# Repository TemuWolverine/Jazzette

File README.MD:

# Jazzette Player
> [!WARNING]  
> **This is work in progress**.  
> I am using this readme as a bit of a scratchpad of parts. Don't assume they're the final parts until this announcement is removed.  
> **This is work in progress**.

I got nerd sniped over on [reddit](https://www.reddit.com/r/homeassistant/comments/1vtjl21/comment/p4xepdl/).  

## PCB
PCB prototype has now been sent off for manufacture.  

## Shell
The shell is still in active development, but here is a render of the vague idea, mimicking the old cassettecorders. 

## BOM

| Part | Quantity     | Note |
|------|-------------|----- |
| [ESP32 S3 Nano](https://s.click.aliexpress.com/e/_c4tw9Hh5) | 1 ||
| [DRV8833](https://www.amazon.com.au/Xlihdzum-DRV8833-H-Bridge-Driver-Module/dp/B0GHQ6YCLV) | 1 |  |
| [N20 DC motor](https://www.aliexpress.com/item/32385310725.html) | 1 |  3v |
| [PCM5100A breakout](https://www.aliexpress.com/item/1005008889469187.html) | 1 | Headphone amp |
| [NFC breakout](https://s.click.aliexpress.com/e/_c3WaMQwL)  | 1 |  |
| [3.12" OLED (256x54) SPI](https://s.click.aliexpress.com/e/_c2IVFyqT) | 1 | White looks best IMO |
| [TOSLINK transmitter](https://s.click.aliexpress.com/e/_c3J5kkCf) | 1 |  |
| [RCA plug](https://s.click.aliexpress.com/e/_c3TPM0xV)     | 1 |       |
| 480ohm resistor    | 1 | 0803 SMD package, used for coax |
| 0.1uF capacitor    | 3 | 0803 SMD package, used for decoupling |
| 6x6 tactile switch    | 4  | SMD|
| 2 pin JST XH right angle | 2 | S2B-XH-A(LF)(SN) |
| 3 pin JST XH right angle | 1 | S3B-XH-A(LF)(SN) |
| 4 pin JST XH right angle | 1 | S4B-XH-A(LF)(SN) |
| 5 pin JST XH right angle | 1 | S5B-XH-A(LF)(SN) |
| [3-way switch](https://www.aliexpress.com/item/1005006780672833.html) | 1 |  |
| 3mm Translucent Black Acrylic | 1 | overlaid over screen |
| 3mm clear acrylic | 1 | Tape door |
| 3d printing filament | | |

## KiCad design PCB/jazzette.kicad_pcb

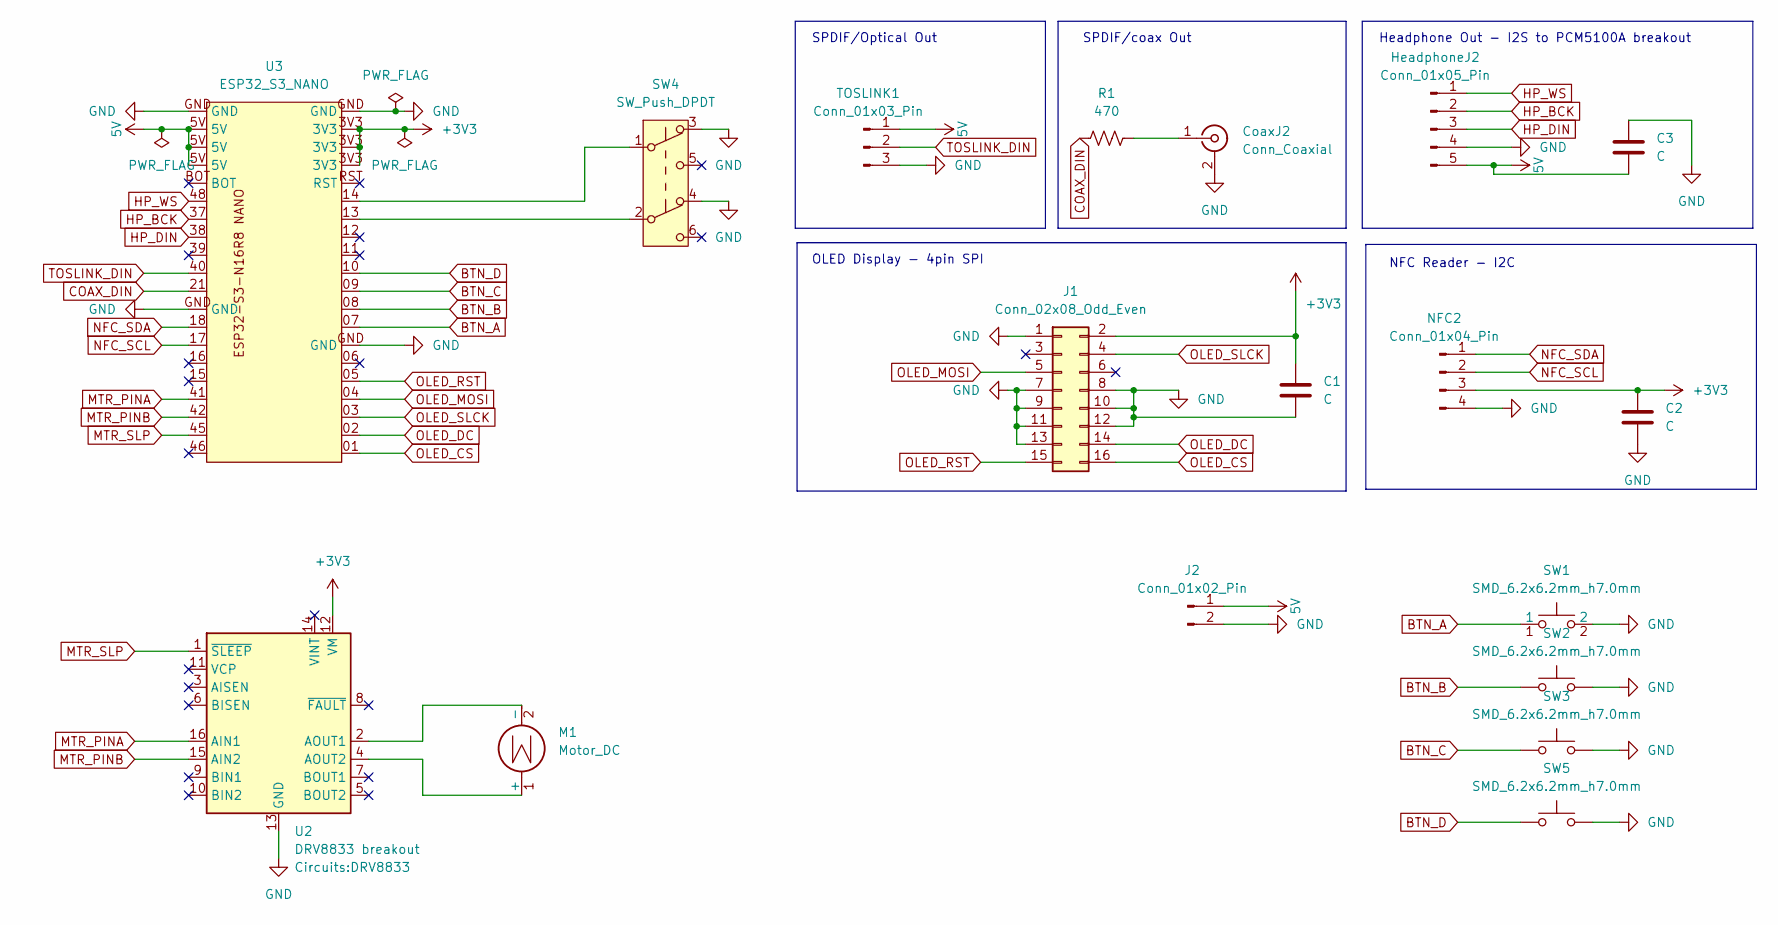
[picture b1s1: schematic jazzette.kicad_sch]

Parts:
C1, C2, C3: C; C_0805_2012Metric
CoaxJ2: Conn_Coaxial; CONN-TH_S2B-XH-A-LF-SN
HeadphoneJ2: Conn_01x05_Pin; CONN-TH_S5B-XH-A-LF-SN
J1: Conn_02x08_Odd_Even; PinSocket_2x08_P2.54mm_Vertical
J2: Conn_01x02_Pin; CONN-TH_DB125-2.54-2P-GN
M1: Motor_DC; CONN-TH_S2B-XH-A-LF-SN
NFC2: Conn_01x04_Pin; CONN-TH_S4B-XH-A-LF-SN
R1: 470; R_0603_1608Metric
SW1, SW2, SW3, SW5: SMD_6.2x6.2mm_h7.0mm; SW-SMD_SH-6X6X4.5H-TP; Mfg Part# 679-2384-2-ND
SW4: SW_Push_DPDT; PinHeader_1x04_P2.54mm_Vertical
TOSLINK1: Conn_01x03_Pin; CONN-TH_S3B-XH-A-LF-SN
U2: DRV8833 breakout; DRV8833
U3: ESP32_S3_NANO

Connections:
5V: C3.1, HeadphoneJ2.5, J2.1, TOSLINK1.1, U3.5V
+3V3: C1.1, C2.1, J1.2, NFC2.3, U2.12 (VM), U3.3V3
BTN_A: SW1.1, U3.07
BTN_B: SW2.1, U3.08
BTN_C: SW3.1, U3.09
BTN_D: SW5.1, U3.10
COAX_DIN: R1.2, U3.21
GND: C1.2, C2.2, C3.2, CoaxJ2.2 (Ext), HeadphoneJ2.4, J1.1, J1.7, J1.8, J1.9, J1.10, J1.11, J1.12, J1.13, J2.2, NFC2.4, SW1.2, SW2.2, SW3.2, SW4.3 (A), SW4.4 (A), SW5.2, TOSLINK1.3, U2.13 (GND), U3.GND
HP_BCK: HeadphoneJ2.2, U3.37
HP_DIN: HeadphoneJ2.3, U3.38
HP_WS: HeadphoneJ2.1, U3.48
MTR_PINA: U2.16 (AIN1), U3.41
MTR_PINB: U2.15 (AIN2), U3.42
MTR_SLP: U2.1 (~SLEEP), U3.45
NFC_SCL: NFC2.2, U3.17
NFC_SDA: NFC2.1, U3.18
unnamed: CoaxJ2.1 (In), R1.1
unnamed: M1.1 (+), U2.4 (AOUT2)
unnamed: M1.2 (-), U2.2 (AOUT1)
unnamed: SW4.1 (B), U3.14
unnamed: SW4.2 (B), U3.13
OLED_CS: J1.16, U3.01
OLED_DC: J1.14, U3.02
OLED_MOSI: J1.5, U3.04
OLED_RST: J1.15, U3.05
OLED_SLCK: J1.4, U3.03
TOSLINK_DIN: TOSLINK1.2, U3.40

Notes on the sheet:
SPDIF/coax Out
SPDIF/Optical Out
Headphone Out - I2S to PCM5100A breakout
NFC Reader - I2C
OLED Display - 4pin SPI

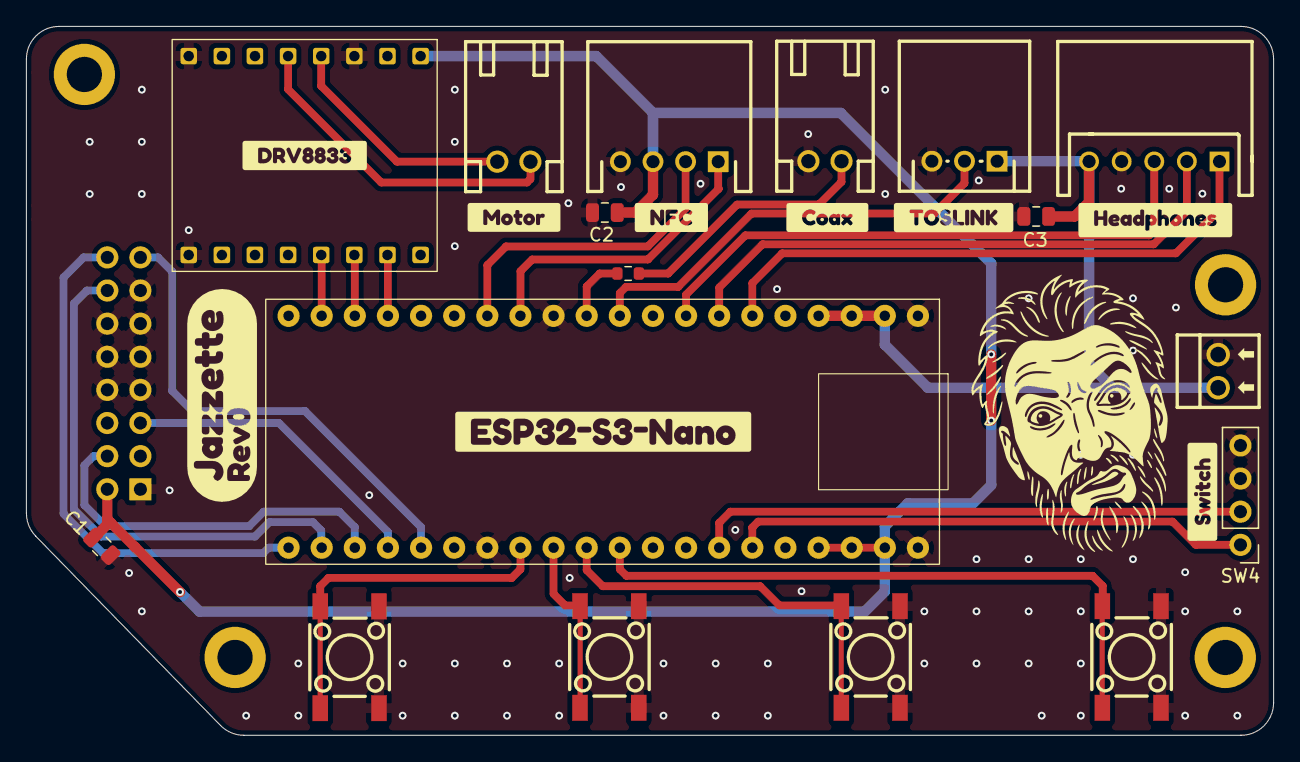
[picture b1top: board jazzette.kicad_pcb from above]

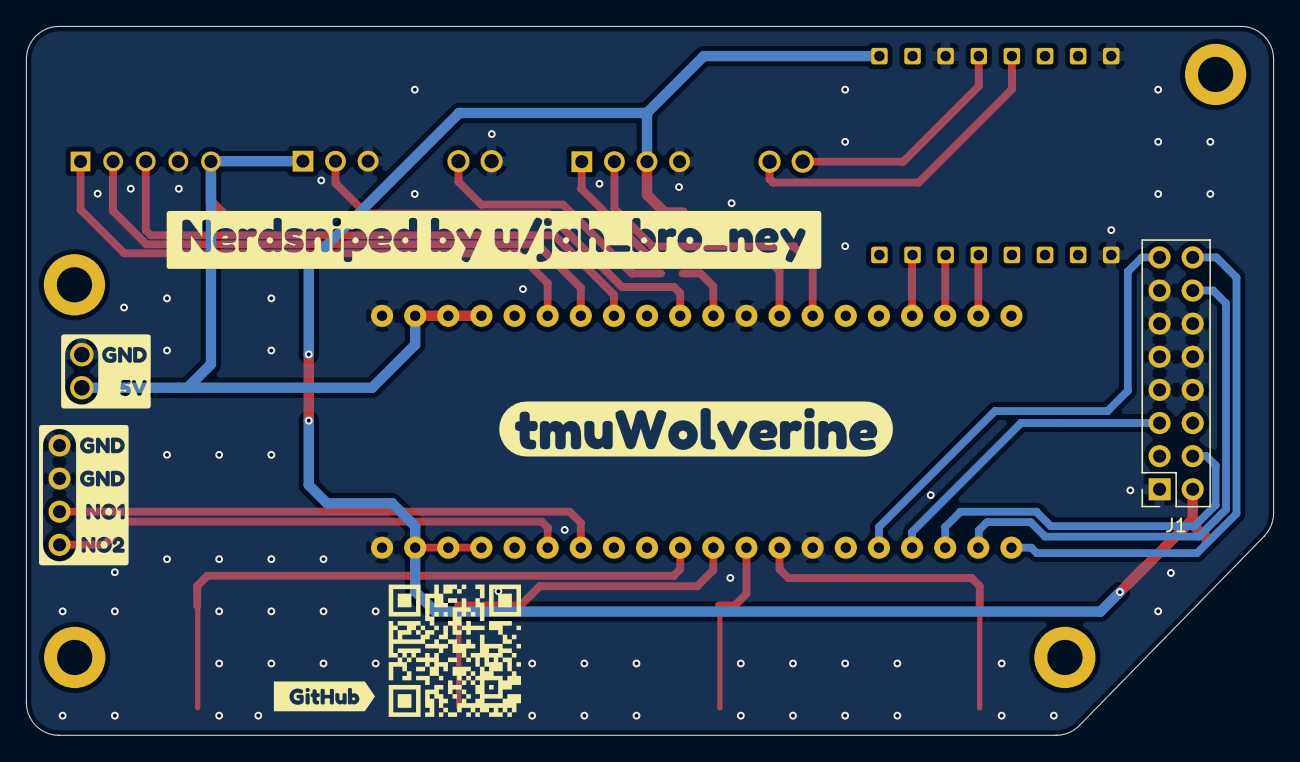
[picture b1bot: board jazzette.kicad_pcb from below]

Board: 2 copper layers, 95.6 x 54.4 mm, 33 parts (7 on the bottom side), 27 nets.

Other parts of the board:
kobee-studio-6A9C82AE: Kobee Studio; kobee-studio-6A9C8293
kobee-studio-6A9DE86C: Kobee Studio; kobee-studio-6A96C1A4
kobee-studio-6A9E5BD7: Kobee Studio; kobee-studio-6A9E5478
kobee-studio-6A9E5E3B: Kobee Studio; kobee-studio-6A9E5C65
kobee-studio-6A9E54C5: Kobee Studio; kobee-studio-6A9E54C5
kobee-studio-6A9E54DB, kobee-studio-6A9E55B7, kobee-studio-6A9E550D, kobee-studio-6A9E5502, kobee-studio-6A9E5517: Kobee Studio; kobee-studio-6A9E54DB
kobee-studio-6A9F86BB: Kobee Studio; kobee-studio-6A9F86BB
kobee-studio-6A9F8757: Kobee Studio; kobee-studio-6A9F8711
kobee-studio-6A97AC47: Kobee Studio; kobee-studio-6A97AC2D
kobee-studio-6A97AC75: Kobee Studio; kobee-studio-6A97AC75
kobee-studio-6A97C0E1: Kobee Studio; kobee-studio-6A97ABF4

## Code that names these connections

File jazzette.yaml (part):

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
  mtr_a: GPIO41
  mtr_b: GPIO42
  mtr_slp: GPIO45

  nfc_sda: GPIO17
  nfc_scl: GPIO18

  headphone_ws: GPIO48
  headphone_bck: GPIO47
  headphone_din: GPIO38

  coax_din: GPIO21
  toslink_din: GPIO40
  
  threewayswitcha: GPIO13
  threewayswitchb: GPIO14
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output:
  - platform: ledc
    id: motor_enable
    pin: ${mtr_slp}
    
  - platform: ledc
    id: motor_forward_pin
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    id: speaker_spdif
    dac_type: external
    i2s_audio_id: i2s_spdif
    i2s_dout_pin: ${coax_din}
    spdif_mode: true
    sample_rate: ${media_sample_rate}
    channel: stereo
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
